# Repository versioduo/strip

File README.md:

# V2 strip
🚦 MIDI LED Strip

Drives a WS2812 LED strip. LEDs are controlled by incoming MIDI notes, the
brightness is controlled by the note velocity. Different MIDI channels use
different colors.

## Screenshot

# Copying
Anyone can use this public domain work without having to seek authorisation, no one can ever own it.

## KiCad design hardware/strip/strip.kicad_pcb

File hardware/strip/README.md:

# V2 strip
🚦 MIDI LED Strip

## Video
[YouTube](https://www.youtube.com/watch?v=P1gKQrn-1O4)

## Schematic
[PDF](strip.pdf)

## Bill Of Materials
[Interactive BOM](https://html-preview.github.io/?url=https://github.com/versioduo/strip/blob/main/hardware/strip/strip-bom.html)

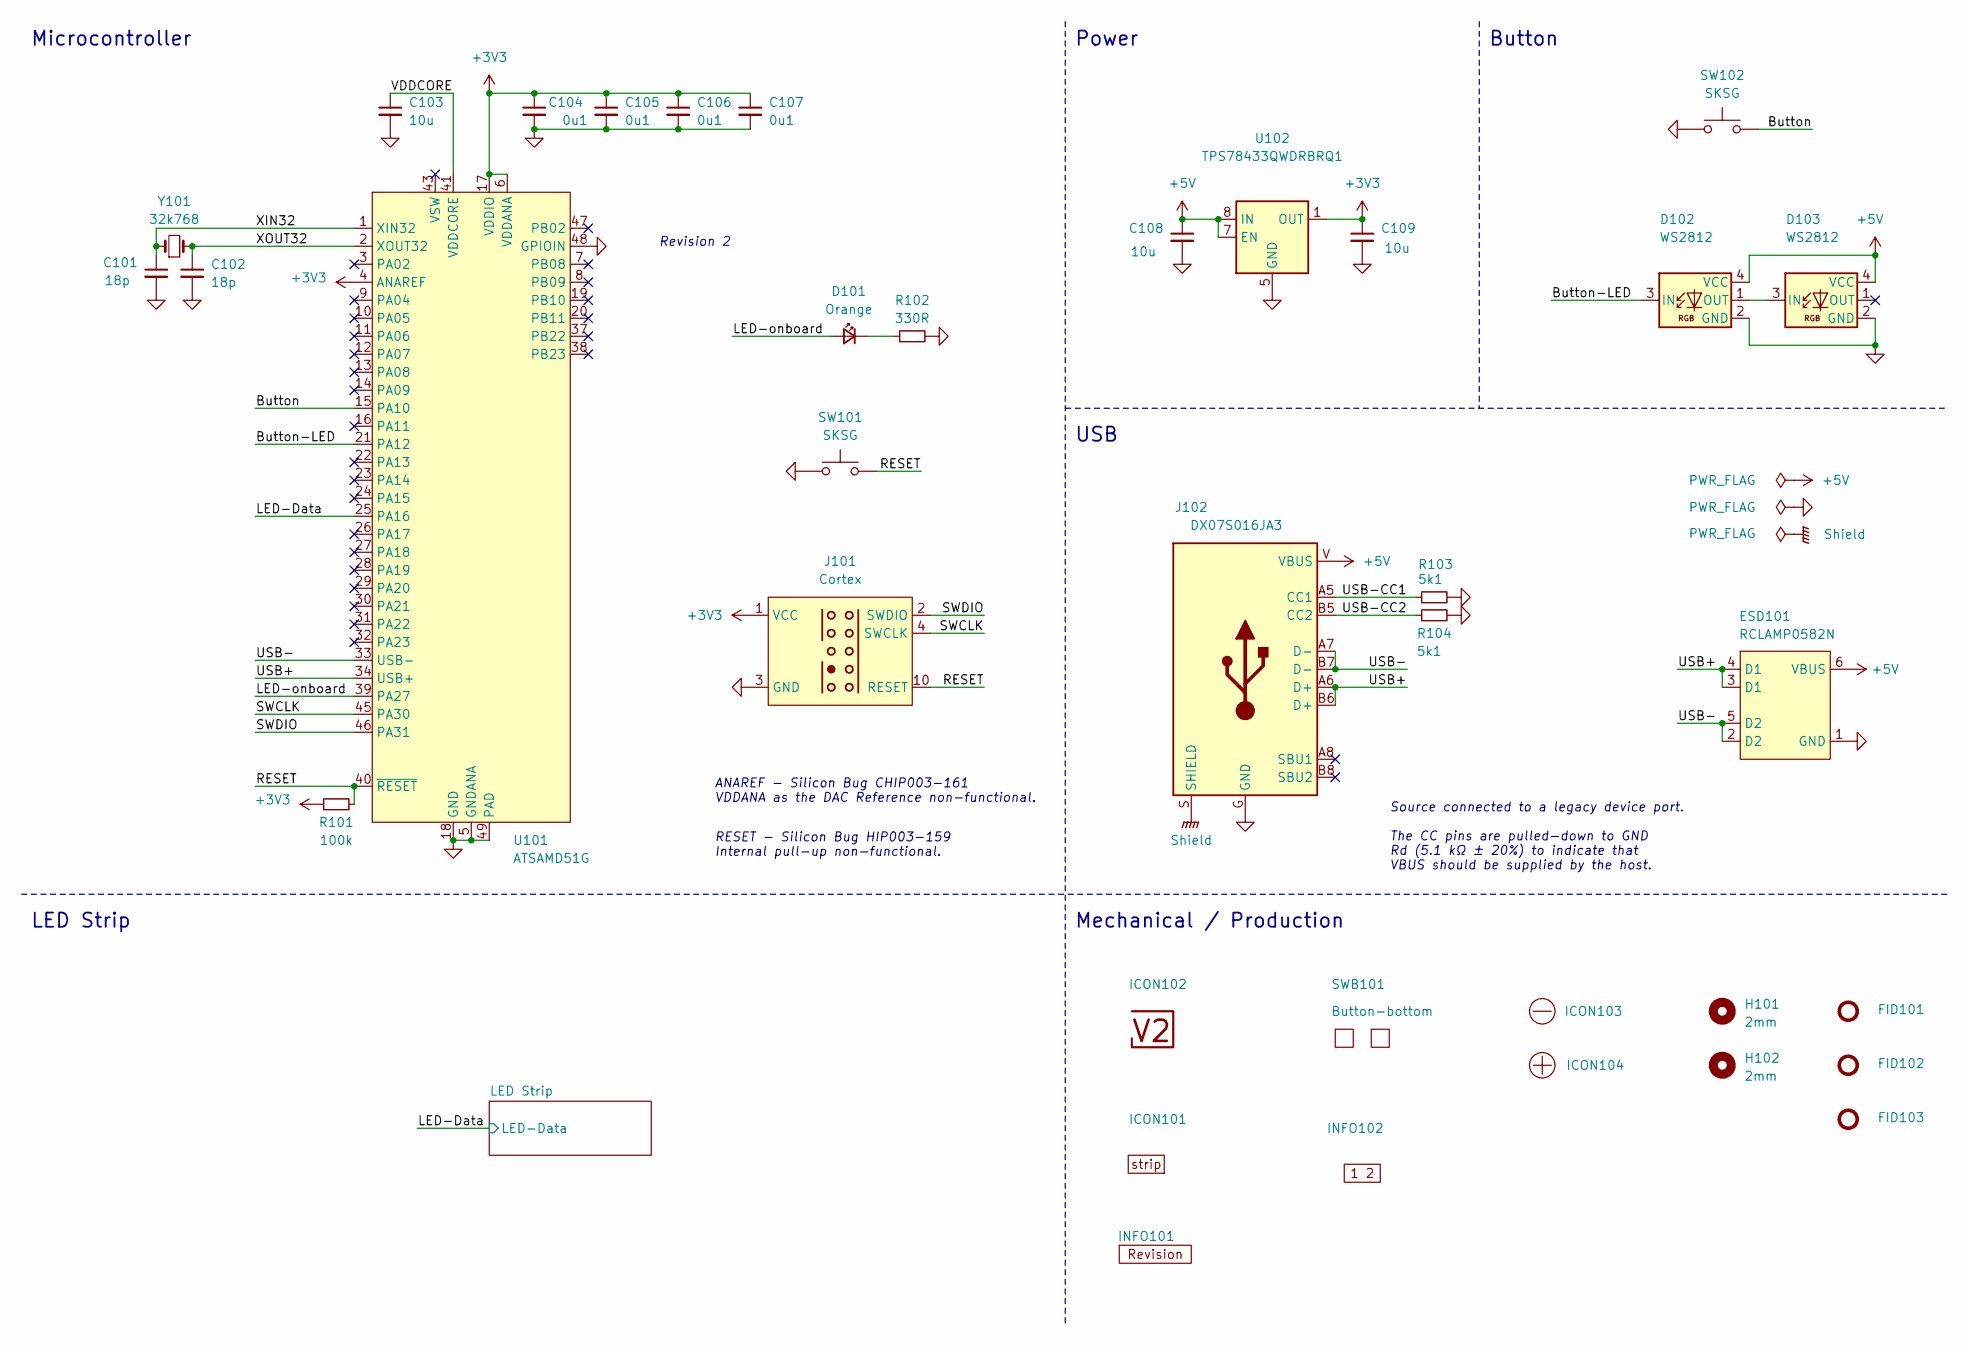
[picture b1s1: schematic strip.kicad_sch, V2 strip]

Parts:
C101, C102: 18p; C_1608; Rating 50V; Mouser 810-CGA3E2C0G1H180J
C103: 10u; C_1608; Rating 10V; Mouser 810-C1608X6S1A106M
C104, C105, C106, C107: 0u1; C_1608; Rating 50V; Mouser 810-CGA3E2X7R1H104MA
C108, C109: 10u; C_2012; Rating 25V; Mouser 810-C2012X5R1E106K
D101: Orange; LED_1608; Rating 605nm; Mouser 755-SML-D12D1WT86
D102, D103: WS2812; WS2812-2020; Rating 15mA; LCSC C965555
ESD101: RCLAMP0582N; SLP1210N6; Rating 20kV; Mouser 947-RCLAMP0582N.TCT
FID101, FID102, FID103: Fiducial_Paste; Fiducial_0.5mm_Mask1mm_Paste
H101, H102: 2mm; MountingHole_2mm
ICON101: Board_strip; Board_strip_Small
ICON102: V2-logo; Logo_Small
ICON103: Minus; Minus_Small
ICON104: Plus; Plus_Small
INFO101: Revision
INFO102: Layer_Numbers-4
J101: Cortex
J102: DX07S016JA3; JAE_DX07S016JA3; Rating USB2.0; Mouser 656-DX07S016JA3R1500
R101: 100k; R_1608; Rating 100mW; Mouser 71-CRCW0603100KFKEAC
R102: 330R; R_1608; Rating 100mW; Mouser 71-CRCW0603330RFKEAC
R103, R104: 5k1; R_1608; Rating 100mW; Mouser 71-CRCW06035K10FKEAC
SW101, SW102: SKSG; Rating 1.6N; Mouser 688-SKSGACE010
SWB101: Button-bottom; PCB_Button-bottom
U101: ATSAMD51G; QFN-48-1EP_7x7mm_P0.5mm_EP5.45x5.45mm_ThermalVias; Rating Cortex-M4F; Mouser 556-ATSAMD51G19AMU
U102: TPS78433QWDRBRQ1; VSON-8-1_3x3mm_P0.65_EP1.65x2.4mm; Rating 300mA; Mouser 595-TPS78433QWDRBRQ1
Y101: 32k768; Crystal_SMD_3215-2Pin_3.2x1.5mm; Rating 10ppm; Mouser 815-ABS0716632.768KT

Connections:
+3V3: C104.1, C105.1, C106.1, C107.1, C109.1, J101.1 (VCC), R101.1, U101.4 (ANAREF), U101.6 (VDDANA), U101.17 (VDDIO), U101.36 (VDDIO), U101.44 (VDDIO), U102.1 (OUT)
+5V: C108.1, D102.4 (VCC), D103.4 (VCC), ESD101.6 (VBUS), J102.V (VBUS), U102.6 (EN), U102.7 (EN), U102.8 (IN); also elsewhere on the board
/Button: SW102.2, U101.15 (PA10)
/Button-LED: D102.3 (IN), U101.21 (PA12)
/LED-Data: U101.25 (PA16); also elsewhere on the board
/LED-onboard: D101.2 (A), U101.39 (PA27)
/RESET: J101.10 (RESET), R101.2, SW101.2, U101.40 (~RESET)
/SWCLK: J101.4 (SWCLK), U101.45 (PA30)
/SWDIO: J101.2 (SWDIO), U101.46 (PA31)
/Shield: J102.S (SHIELD)
/USB+: ESD101.3 (D1), ESD101.4 (D1), J102.A6 (D+), J102.B6 (D+), U101.34 (USB+)
/USB-: ESD101.2 (D2), ESD101.5 (D2), J102.A7 (D-), J102.B7 (D-), U101.33 (USB-)
/USB-CC1: J102.A5 (CC1), R103.1
/USB-CC2: J102.B5 (CC2), R104.1
/VDDCORE: C103.1, U101.41 (VDDCORE)
/XIN32: C101.1, U101.1 (XIN32), Y101.1
/XOUT32: C102.1, U101.2 (XOUT32), Y101.2
GND: C101.2, C102.2, C103.2, C104.2, C105.2, C106.2, C107.2, C108.2, C109.2, D102.2 (GND), D103.2 (GND), ESD101.1 (GND), J101.3 (GND), J101.5 (GND), J102.G (GND), R102.2, R103.2, R104.2, SW101.1, SW102.1, U101.5 (GNDANA), U101.18 (GND), U101.35 (GND), U101.42 (GND), U101.48 (GPIOIN), U101.49 (PAD), U102.5 (GND), U102.9 (GND); also elsewhere on the board
unnamed: D101.1 (K), R102.1
unnamed: D102.1 (OUT), D103.3 (IN)

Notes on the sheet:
ANAREF - ﻿Silicon Bug CHIP003-161 VDDANA as the DAC Reference non-functional.
RESET - ﻿Silicon Bug HIP003-159 Internal pull-up non-functional.
﻿Source connected to a legacy device port. The CC pins are pulled-down to GND Rd (5.1 kΩ ± 20%) to indicate that VBUS should be supplied by the host.
Button
Revision 2
Power
Mechanical / Production
Microcontroller
USB
LED Strip

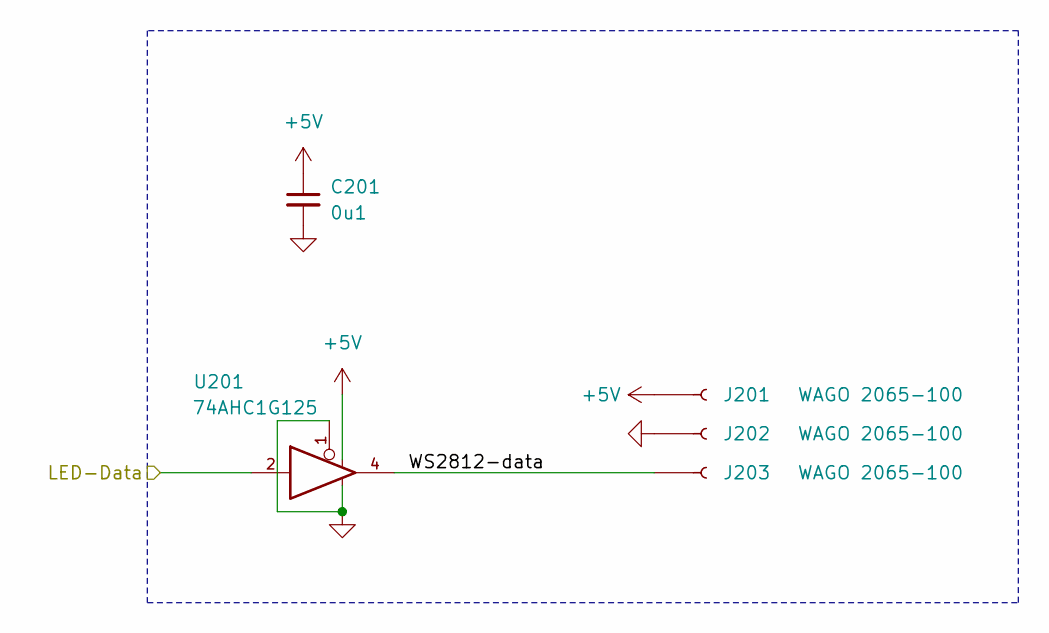
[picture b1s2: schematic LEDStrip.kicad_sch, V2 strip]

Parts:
C201: 0u1; C_1608; Rating 50V; Mouser 810-CGA3E2X7R1H104MA
J201, J202, J203: WAGO 2065-100; 2065-100; Rating 9A
U201: 74AHC1G125; SOT-23-5; Rating 8mA; Mouser 595-SN74AHC1G125DBVR

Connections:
+5V: C201.1, J201.1, U201.5; also elsewhere on the board
/LED Strip/WS2812-data: J203.1, U201.4
/LED-Data: U201.2; also elsewhere on the board
GND: C201.2, J202.1, U201.1, U201.3; also elsewhere on the board

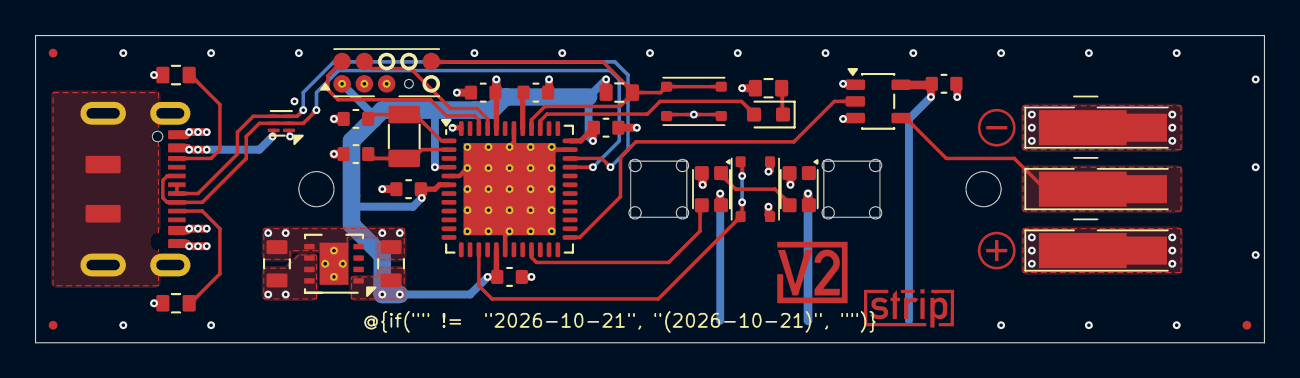
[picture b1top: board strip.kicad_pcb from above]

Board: 4 copper layers, 70.0 x 17.5 mm, 41 parts (0 on the bottom side), 20 nets.

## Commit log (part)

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2022-10-13 Import
2022-10-23 Add Note Aftertouch support
2023-04-08 Update Configuration and prioritize Bar over Notes
2023-06-02 Add ability to light up all C notes as a guide
2023-06-07 Update C notes when writing the settings
2024-01-21 ArduinoJson 7
2025-12-29 Colour
2026-02-13 Replace Order_Number
2026-02-15 Update Library
2026-03-14 Update ESD suppressor
2026-05-11 Good Bye Imperial
2026-06-23 Update V2MIDI API
